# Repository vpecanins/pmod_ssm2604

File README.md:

# PMOD_SSM2604
Audio Codec PMOD board for FPGA

This is a small PMOD board that adds stereo ADC and DAC to your FPGA project. 
It is based around the SSM2604 audio codec from Analog Devices. The dimensions
of the board and connector pinout follow the rules for PMOD from Digilent.

[SSM2604 audio codec from Analog Devices](https://www.analog.com/en/products/ssm2604.html)

[How to design a PMOD - Digilent](https://blog.digilentinc.com/how-to-design-a-pmod-best-practices/)

## Specifications
- Two channel input ADC 24 bits
- Two channel output DAC 24 bits
- Sample rate configurable up to 96 kHz
- Onboard 12.288 master clock crystal oscillator
- Audio clock can be generated by FPGA changing R9/R10 solder bridges
- I2C configuration interface

## Status of the project

The board has been manufactured at PCBWay and successfully tested in MAX1000 FPGA board

## Pictures

## Pinout

Pinout is written on the bottom silk screen of the board.

1. 3V3 supply for digital and analog circuits
2. 3V3 supply for digital and analog circuits
3. Ground
4. Ground
5. ADCDAT: ADC sample data provided by SSM2604 (I2S interface)
6. ADCLRC: ADC left/right clock provided by FPGA (I2S interface)
7. DACDAT: DAC sample data provided by FPGA (I2S interface)
8. DACLRC: DAC left/right clock provided by FPGA (I2S interface)
9. BCLK: Bit clock provided by FPGA (I2S interface) **Must be derived from AUDIO_CLK**
10. AUDIO_CLK: Master clock 12.288 MHz. Generated by SSM2604 oscillator.
11. SCLK: I2C interface SCL
12. SDIN: I2C interface SDA

Pin names keep the nomenclature from Analog Devices datasheet

## License
	
    Copyright (C) 2020  vpecanins

    This program is free software: you can redistribute it and/or modify
    it under the terms of the GNU General Public License as published by
    the Free Software Foundation, either version 3 of the License, or
    (at your option) any later version.

    This program is distributed in the hope that it will be useful,
    but WITHOUT ANY WARRANTY; without even the implied warranty of
    MERCHANTABILITY or FITNESS FOR A PARTICULAR PURPOSE.  See the
    GNU General Public License for more details.

    You should have received a copy of the GNU General Public License
    along with this program.  If not, see <https://www.gnu.org/licenses/>.

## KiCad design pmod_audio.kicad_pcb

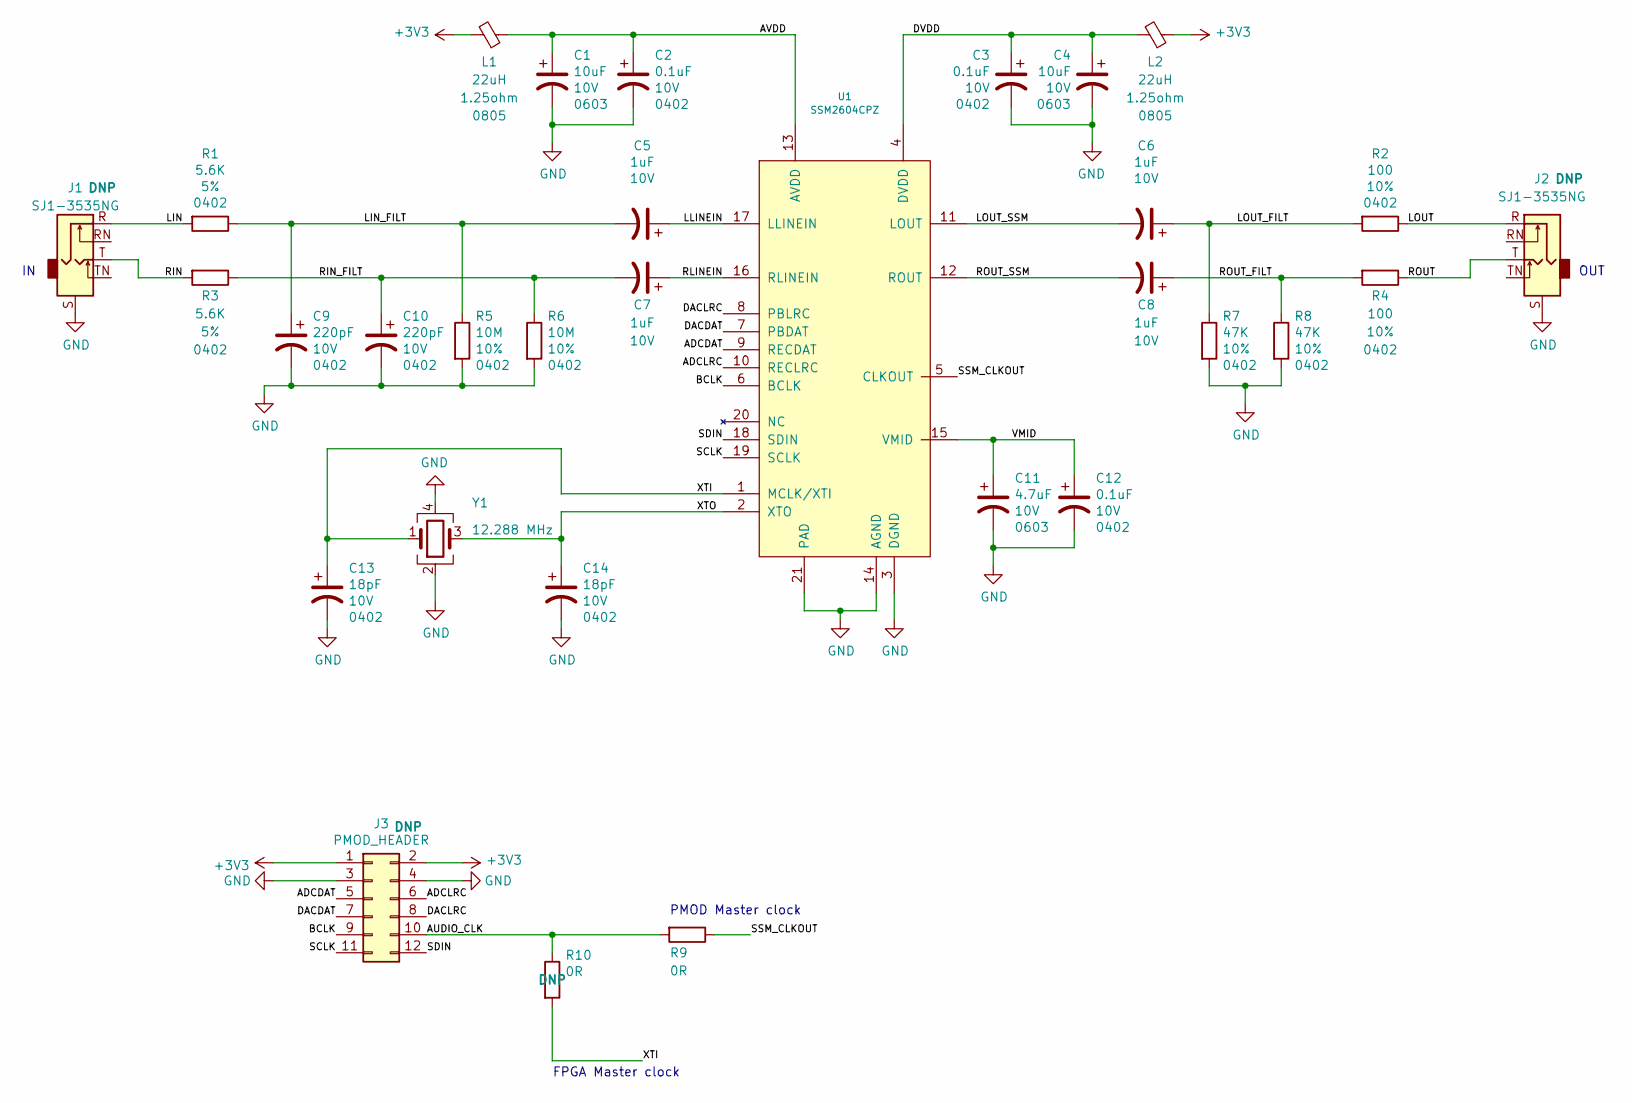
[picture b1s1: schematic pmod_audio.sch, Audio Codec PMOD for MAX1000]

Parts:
C1, C4: 10uF; C_0603_1608Metric; Voltage 10V
C2, C3, C12: 0.1uF; C_0402_1005Metric; Voltage 10V
C5, C6, C7, C8: 1uF; CP_Elec_4x5.4; Voltage 10V
C9, C10: 220pF; C_0402_1005Metric; Voltage 10V
C11: 4.7uF; C_0603_1608Metric; Voltage 10V
C13, C14: 18pF; C_0402_1005Metric; Voltage 10V
J1, J2: SJ1-3535NG; Jack_3.5mm_CUI_SJ1-3535NG_Horizontal
J3: PMOD_HEADER; PinHeader_2x06_P2.54mm_Horizontal
L1, L2: 22uH; L_0805_2012Metric
R1, R3: 5.6K; R_0402_1005Metric; Tolerance 5%
R2, R4: 100; R_0402_1005Metric; Tolerance 10%
R5, R6: 10M; R_0402_1005Metric; Tolerance 10%
R7, R8: 47K; R_0402_1005Metric; Tolerance 10%
R9, R10: 0R; R_0402_1005Metric; Tolerance 10%
U1: SSM2604CPZ; QFN-20-1EP_SSM2604
Y1: 12.288 MHz; Crystal_SMD_3225-4Pin_3.2x2.5mm

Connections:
+3V3: J3.1, J3.2, L1.2, L2.1
/ADCDAT: J3.5, U1.9 (RECDAT)
/ADCLRC: J3.6, U1.10 (RECLRC)
/AUDIO_CLK: J3.10, R9.2, R10.1
/AVDD: C1.1, C2.1, L1.1, U1.13 (AVDD)
/BCLK: J3.9, U1.6 (BCLK)
/DACDAT: J3.7, U1.7 (PBDAT)
/DACLRC: J3.8, U1.8 (PBLRC)
/DVDD: C3.1, C4.1, L2.2, U1.4 (DVDD)
/LIN: J1.R, R1.2
/LIN_FILT: C5.2, C9.1, R1.1, R5.1
/LLINEIN: C5.1, U1.17 (LLINEIN)
/LOUT: J2.R, R2.1
/LOUT_FILT: C6.1, R2.2, R7.1
/LOUT_SSM: C6.2, U1.11 (LOUT)
/RIN: J1.T, R3.2
/RIN_FILT: C7.2, C10.1, R3.1, R6.1
/RLINEIN: C7.1, U1.16 (RLINEIN)
/ROUT: J2.T, R4.1
/ROUT_FILT: C8.1, R4.2, R8.1
/ROUT_SSM: C8.2, U1.12 (ROUT)
/SCLK: J3.11, U1.19 (SCLK)
/SDIN: J3.12, U1.18 (SDIN)
/SSM_CLKOUT: R9.1, U1.5 (CLKOUT)
/VMID: C11.1, C12.1, U1.15 (VMID)
/XTI: C13.1, R10.2, U1.1 (MCLK/XTI), Y1.1
/XTO: C14.1, U1.2 (XTO), Y1.3
GND: C1.2, C2.2, C3.2, C4.2, C9.2, C10.2, C11.2, C12.2, C13.2, C14.2, J1.S, J2.S, J3.3, J3.4, R5.2, R6.2, R7.2, R8.2, U1.3 (DGND), U1.14 (AGND), U1.21 (PAD), Y1.2, Y1.4

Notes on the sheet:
FPGA Master clock
PMOD Master clock
OUT

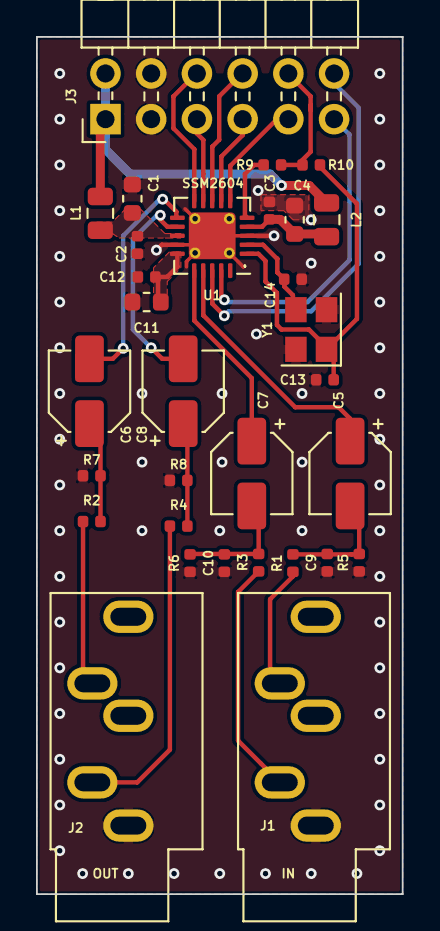
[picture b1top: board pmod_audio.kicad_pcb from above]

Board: 2 copper layers, 20.3 x 47.6 mm, 31 parts (0 on the bottom side), 28 nets.

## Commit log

2020-05-05 add kicad project
